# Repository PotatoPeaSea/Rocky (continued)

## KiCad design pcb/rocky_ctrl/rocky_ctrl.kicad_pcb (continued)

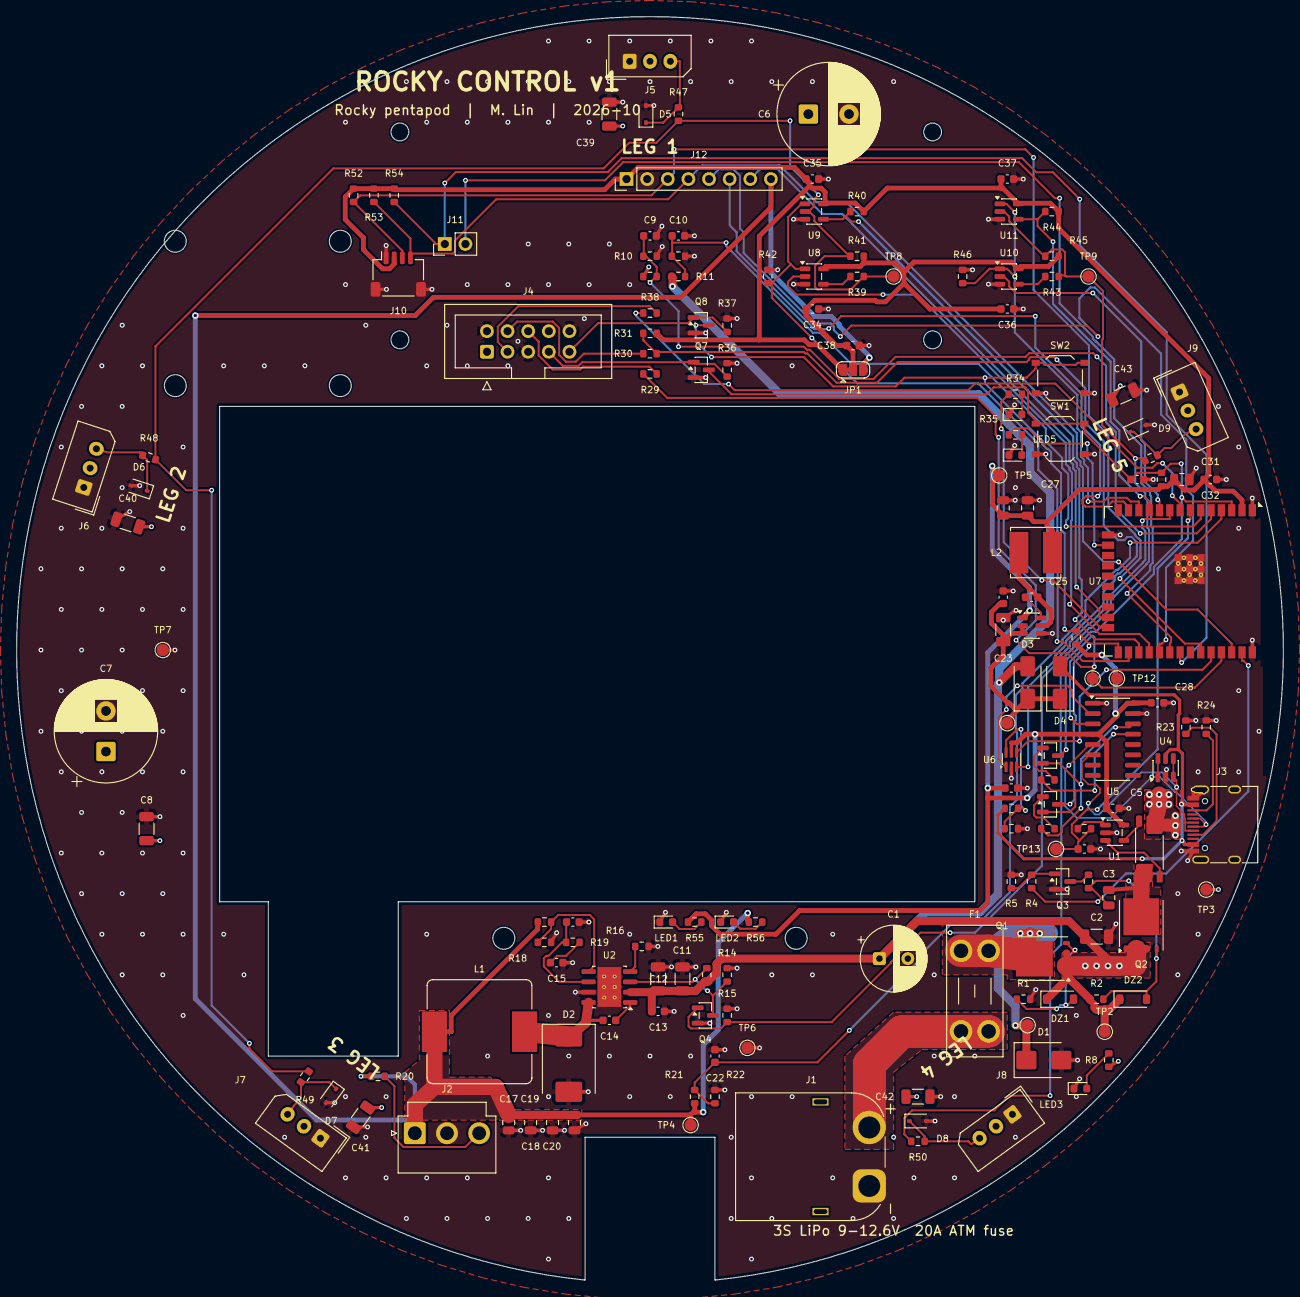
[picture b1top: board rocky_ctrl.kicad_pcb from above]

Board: 4 copper layers, 156.0 x 155.6 mm, 173 parts (0 on the bottom side), 84 nets.

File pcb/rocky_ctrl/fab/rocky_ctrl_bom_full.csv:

"Reference","Value","Footprint","LCSC","MPN","QUANTITY"
"C1","220u 35V","Capacitor_THT:CP_Radial_D8.0mm_P3.50mm","","Panasonic EEU-FR1V221 (220 uF 35 V, 8x11.5)","1"
"C2,C8,C11,C12,C23","10u 50V","Capacitor_SMD:C_1206_3216Metric","","GRM31CR61H106KA12 (10 uF 50 V X5R 1206)","5"
"C3","220n 50V","Capacitor_SMD:C_0805_2012Metric","","220 nF 50 V X7R 0805 (Miller soft-start)","1"
"C4","10n","Capacitor_SMD:C_0603_1608Metric","C57112","10n","1"
"C5,C9,C10,C13,C14,C22,C24,C25,C28,C29,C32,C34,C35,C36,C37","100n","Capacitor_SMD:C_0603_1608Metric","C14663","100n","15"
"C6,C7","1000u 35V","Capacitor_THT:CP_Radial_D12.5mm_P5.00mm","","Panasonic EEU-FR1V102 (1000 uF 35 V, 12.5x20, 2.2 A ripple)","2"
"C15","3.9n","Capacitor_SMD:C_0603_1608Metric","","3.9n","1"
"C16","39p","Capacitor_SMD:C_0603_1608Metric","","39p","1"
"C17,C18,C19,C20,C26,C27,C31","22u","Capacitor_SMD:C_0805_2012Metric","C45783","22 uF 25 V X5R 0805","7"
"C30,C38","1u","Capacitor_SMD:C_0603_1608Metric","C15849","1u","2"
"C39,C40,C41,C42,C43","22u","Capacitor_SMD:C_1206_3216Metric","","22 uF 25 V X5R 1206","5"
"D1","SMBJ15A","Diode_SMD:D_SMB","","SMBJ15A (15 V stand-off unidirectional TVS)","1"
"D2","B540C","Diode_SMD:D_SMC","","B540C-13-F (40 V 5 A Schottky, SMC)","1"
"D3,D4","SS34","Diode_SMD:D_SMA","C8678","SS34","2"
"D5,D6,D7,D8,D9","PESD5V0S1BB","Diode_SMD:D_SOD-323","","PESD5V0S1BB (bidirectional ESD, SOD-323)","5"
"DZ1,DZ2","BZT52C10","Diode_SMD:D_SOD-123","","BZT52C10 (10 V Vgs clamp)","2"
"F1","20A ATM","Fuse:Fuseholder_Blade_Mini_Keystone_3568","","Keystone 3568 + 20 A mini blade fuse","1"
"J1","XT60PW-M","Connector_AMASS:AMASS_XT60PW-M_1x02_P7.20mm_Horizontal","","AMASS XT60PW-M","1"
"J2","Pi 5V","Connector_JST:JST_VH_B3P-VH-B_1x03_P3.96mm_Vertical","","JST B3P-VH-B (to USB-C pigtail into the Pi 5)","1"
"J3","USB-C","Connector_USB:USB_C_Receptacle_HRO_TYPE-C-31-M-12","C165948","HRO TYPE-C-31-M-12","1"
"J4","Pi GPIO 5-14","Connector_IDC:IDC-Header_2x05_P2.54mm_Vertical","","2x5 2.54 mm box header (ribbon to Pi pins 5-14)","1"
"J5","LEG1","Connector_Molex:Molex_SPOX_5267-03A_1x03_P2.50mm_Vertical","","Molex 5267-03A (or 2.50 mm ""5264"" 3P vertical header)","1"
"J6","LEG2","Connector_Molex:Molex_SPOX_5267-03A_1x03_P2.50mm_Vertical","","Molex 5267-03A (or 2.50 mm ""5264"" 3P vertical header)","1"
"J7","LEG3","Connector_Molex:Molex_SPOX_5267-03A_1x03_P2.50mm_Vertical","","Molex 5267-03A (or 2.50 mm ""5264"" 3P vertical header)","1"
"J8","LEG4","Connector_Molex:Molex_SPOX_5267-03A_1x03_P2.50mm_Vertical","","Molex 5267-03A (or 2.50 mm ""5264"" 3P vertical header)","1"
"J9","LEG5","Connector_Molex:Molex_SPOX_5267-03A_1x03_P2.50mm_Vertical","","Molex 5267-03A (or 2.50 mm ""5264"" 3P vertical header)","1"
"J10","STEMMA QT","Connector_JST:JST_SH_SM04B-SRSS-TB_1x04-1MP_P1.00mm_Horizontal","C160390","JST SM04B-SRSS-TB (STEMMA QT to Adafruit BNO085)","1"
"J11","IMU INT/RST","Connector_PinHeader_2.54mm:PinHeader_1x02_P2.54mm_Vertical","","1x2 2.54 mm header","1"
"J12","SPARE","Connector_PinHeader_2.54mm:PinHeader_1x08_P2.54mm_Vertical","","1x8 2.54 mm header","1"
"L1","4.7u","Inductor_SMD:L_Bourns_SRP1245A","","Bourns SRP1245A-4R7M (4.7 uH, Isat 21 A)","1"
"L2","4.7u","Inductor_SMD:L_Bourns_SRN6045TA","","Bourns SRN6045TA-4R7M (4.7 uH 3.4 A)","1"
"LED1","GREEN 3V3","LED_SMD:LED_0603_1608Metric","C72043","GREEN 3V3","1"
"LED2","GREEN 5V","LED_SMD:LED_0603_1608Metric","C72043","GREEN 5V","1"
"LED3","RED SERVO","LED_SMD:LED_0603_1608Metric","C2286","RED SERVO","1"
"LED4","BLUE","LED_SMD:LED_0603_1608Metric","C72041","BLUE","1"
"LED5","YELLOW","LED_SMD:LED_0603_1608Metric","C72038","YELLOW","1"
"Q1,Q2","BSC030P03NS3","Package_TO_SOT_SMD:TDSON-8-1","","Infineon BSC030P03NS3G (-30 V, 3.0 mOhm)","2"
"Q3,Q5,Q6","MMBT3904","Package_TO_SOT_SMD:SOT-23","C20526","MMBT3904","3"
"Q4,Q7,Q8","2N7002","Package_TO_SOT_SMD:SOT-23","C8545","2N7002","3"
"R1,R4,R18,R20,R22,R25,R26,R27,R32,R33,R40,R41,R42,R44,R45,R46,R54","10k","Resistor_SMD:R_0603_1608Metric","C25804","10k 1% 0603","17"
"R2,R5,R9,R11,R13,R15,R31,R36,R37","100k","Resistor_SMD:R_0603_1608Metric","C25803","100k 1% 0603","9"
"R3","33k","Resistor_SMD:R_0603_1608Metric","C4216","33k 1% 0603","1"
"R6","1m","Resistor_SMD:R_Shunt_Vishay_WSK2512_6332Metric_T1.19mm","","Vishay WSK25121L000FEA (1 mOhm 1 % 2512 4-terminal)","1"
"R7,R29,R30,R34,R35,R38,R55","1k","Resistor_SMD:R_0603_1608Metric","C21190","1k 1% 0603","7"
"R8,R52,R53","4.7k","Resistor_SMD:R_0603_1608Metric","C23162","4.7k 1% 0603","3"
"R10,R12,R21,R28","22k","Resistor_SMD:R_0603_1608Metric","C31850","22k 1% 0603","4"
"R14","18k","Resistor_SMD:R_0603_1608Metric","","18k 1% 0603","1"
"R16","191k","Resistor_SMD:R_0603_1608Metric","","191k 1% 0603","1"
"R17","53.6k","Resistor_SMD:R_0603_1608Metric","","53.6k 1% 0603","1"
"R19","16k","Resistor_SMD:R_0603_1608Metric","","16k 1% 0603","1"
"R23,R24","5.1k","Resistor_SMD:R_0603_1608Metric","C23186","5.1k 1% 0603","2"
"R39,R43","22","Resistor_SMD:R_0603_1608Metric","C23345","22 1% 0603","2"
"R47,R48,R49,R50,R51","33","Resistor_SMD:R_0603_1608Metric","C23140","33 1% 0603","5"
"R56","2.2k","Resistor_SMD:R_0603_1608Metric","C4190","2.2k 1% 0603","1"
"SW1","EN","Button_Switch_SMD:SW_Push_1P1T_XKB_TS-1187A","C318884","XKB TS-1187A-B-A-B","1"
"SW2","BOOT","Button_Switch_SMD:SW_Push_1P1T_XKB_TS-1187A","C318884","XKB TS-1187A-B-A-B","1"
"U1","INA180A3","Package_TO_SOT_SMD:SOT-23-5","","INA180A3IDBVR (100 V/V)","1"
"U2","TPS54560B","Package_SO:Texas_R-PDSO-G8_EP2.95x4.9mm_Mask2.4x3.1mm_ThermalVias","","TPS54560BDDAR","1"
"U3","AP63203WU","Package_TO_SOT_SMD:TSOT-23-6","","AP63203WU-7","1"
"U4","USBLC6-2SC6","Package_TO_SOT_SMD:SOT-23-6","C7519","USBLC6-2SC6","1"
"U5","CH340C","Package_SO:SOIC-16_3.9x9.9mm_P1.27mm","C84681","CH340C","1"
"U6","74LVC1G3157","Package_TO_SOT_SMD:SOT-363_SC-70-6","","SN74LVC1G3157DCKR (S=L: B1=Pi, S=H: B2=USB)","1"
"U7","ESP32-WROOM-32E-N8","RF_Module:ESP32-WROOM-32E","C701342","ESP32-WROOM-32E-N8 (8 MB)","1"
"U8,U10","SN74LV1T126","Package_TO_SOT_SMD:SOT-23-5","","SN74LV1T126DBVR (TX driver, OE high)","2"
"U9,U11","SN74LV1T125","Package_TO_SOT_SMD:SOT-23-5","","SN74LV1T125DBVR (RX buffer, OE low)","2"

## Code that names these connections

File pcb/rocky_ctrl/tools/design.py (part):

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P('U7', 'RF_Module:ESP32-WROOM-32E', 'ESP32-WROOM-32E-N8', 'RF_Module:ESP32-WROOM-32E',
  {'1': 'GND', '15': 'GND', '38': 'GND', '39': 'GND', '2': '+3V3', '3': 'EN',
   '4': 'V5_SENSE', '5': 'VSRV_SENSE', '6': 'VBAT_SENSE', '7': 'ISERVO', '8': 'PI_ATTN', '9': 'PI_PWR_OFF',
   '10': 'BUSB_TX', '11': 'BUSB_RX', '12': 'BUSB_DIR', '13': 'GPIO14', '14': '', '16': 'LED_USER',
   '17': '', '18': '', '19': '', '20': '', '21': '', '22': '', '32': '',
   '23': 'GPIO15', '24': 'LED_STAT', '25': 'BOOT', '26': 'BUSA_DIR', '27': 'BUSA_RX', '28': 'BUSA_TX',
   '29': 'GPIO5', '30': 'IMU_RST', '31': 'IMU_INT', '33': 'SDA', '34': 'ESP_RX0', '35': 'ESP_TX0',
   '36': 'SCL', '37': 'SERVO_EN'}, 'mcu', 'C701342', 'ESP32-WROOM-32E-N8 (8 MB)')
C('C30', '1u', 'EN', 'GND', 'mcu', CL['1u'])
R('R32', '10k', '+3V3', 'EN', 'mcu', RL['10k'])
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
# =========================================================================== PI LINK
P('J4', 'Connector_Generic:Conn_02x05_Odd_Even', 'Pi GPIO 5-14', 'Connector_IDC:IDC-Header_2x05_P2.54mm_Vertical',
  {'1': '', '2': 'GND', '3': 'PI_GPIO4', '4': 'PI_TXD_RAW', '5': 'GND', '6': 'PI_RXD', '7': 'PI_RST', '8': '',
   '9': 'PI_BOOT', '10': 'GND'}, 'pi', '', '2x5 2.54 mm box header (ribbon to Pi pins 5-14)')
R('R29', '1k', 'ESP_TX0', 'PI_RXD', 'pi', RL['1k'])
R('R30', '1k', 'PI_TXD_RAW', 'PI_TXD', 'pi', RL['1k'])
R('R31', '100k', 'PI_TXD', '+3V3', 'pi', RL['100k'])
R('R38', '1k', 'PI_ATTN', 'PI_GPIO4', 'pi', RL['1k'])
P('Q7', 'Transistor_FET:2N7002', '2N7002', SOT23, {'1': 'PI_RST', '2': 'GND', '3': 'EN'}, 'pi', 'C8545')
P('Q8', 'Transistor_FET:2N7002', '2N7002', SOT23, {'1': 'PI_BOOT', '2': 'GND', '3': 'BOOT'}, 'pi', 'C8545')
R('R36', '100k', 'PI_RST', 'GND', 'pi', RL['100k'])
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R('R53', '4.7k', 'SCL', '+3V3', 'io', RL['4.7k'])
R('R54', '10k', 'IMU_INT', '+3V3', 'io', RL['10k'])
P('J12', 'Connector_Generic:Conn_01x08', 'SPARE', 'Connector_PinHeader_2.54mm:PinHeader_1x08_P2.54mm_Vertical',
  {'1': '+3V3', '2': 'GND', '3': 'SDA', '4': 'SCL', '5': 'GPIO5', '6': 'GPIO14', '7': 'GPIO15', '8': '+5V'}, 'io', '',
  '1x8 2.54 mm header')
R('R55', '1k', '+3V3', 'LED1_A', 'io', RL['1k'])
P('LED1', 'Device:LED', 'GREEN 3V3', LED0603, {'1': 'GND', '2': 'LED1_A'}, 'io', 'C72043')
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GPIO_MAP = [
    ('EN', 'EN', 'Reset: 10k/1u RC, EN button, CH340 auto-reset, Pi GPIO17 via 2N7002'),
    ('IO0', 'BOOT', 'Strap. BOOT button, CH340 auto-reset, Pi GPIO27 via 2N7002'),
    ('IO1 / TXD0', 'ESP_TX0', 'UART0 TX to CH340C RXD and (1k) Pi GPIO15/RXD'),
    ('IO3 / RXD0', 'ESP_RX0', 'UART0 RX from 74LVC1G3157 mux: CH340C when USB VBUS present, else Pi GPIO14/TXD'),
    ('IO2', 'LED_STAT', 'Strap (must float/low at boot; LED to GND is fine). Blue status LED'),
    ('IO4', 'BUSA_DIR', 'UART1 RTS (RS485 half-duplex mode): high = transmit on bus A'),
    ('IO16', 'BUSA_RX', 'UART1 RX (bus A: legs 1-3, servo IDs 1-9)'),
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    ('IO27', 'BUSB_DIR', 'UART2 RTS: high = transmit on bus B'),
    ('IO23', 'SERVO_EN', 'Servo rail enable, active high, 100k pull-down on the switch side (off at reset)'),
    ('IO33', 'PI_PWR_OFF', 'High = 5 V Pi buck disabled (100k pull-down: Pi on by default)'),
    ('IO32', 'PI_ATTN', 'ESP32 -> Pi GPIO4 attention/IRQ line (1k series)'),
    ('IO21', 'SDA', 'I2C SDA (STEMMA QT IMU, spare header), 4.7k pull-up'),
    ('IO22', 'SCL', 'I2C SCL, 4.7k pull-up'),
    ('IO19', 'IMU_INT', 'BNO085 INT (10k pull-up)'),
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    ('IO36 / SENSOR_VP', 'V5_SENSE', 'ADC1_CH0: 5 V rail, 22k/10k (5.1 V -> 1.59 V)'),
    ('IO39 / SENSOR_VN', 'VSRV_SENSE', 'ADC1_CH3: switched servo rail, 100k/22k'),
    ('IO13', 'LED_USER', 'Yellow user LED'),
    ('IO5', 'GPIO5', 'Spare header (strap: keep high or floating at boot)'),
    ('IO14', 'GPIO14', 'Spare header'),
    ('IO15', 'GPIO15', 'Spare header (strap: boot log enable)'),
    ('IO12', '-', 'Not connected (strap MTDI must be low at boot for 3.3 V flash)'),
]

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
